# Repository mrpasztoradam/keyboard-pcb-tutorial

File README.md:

# keyboard-pcb-tutorial
 Keyboard design from 0

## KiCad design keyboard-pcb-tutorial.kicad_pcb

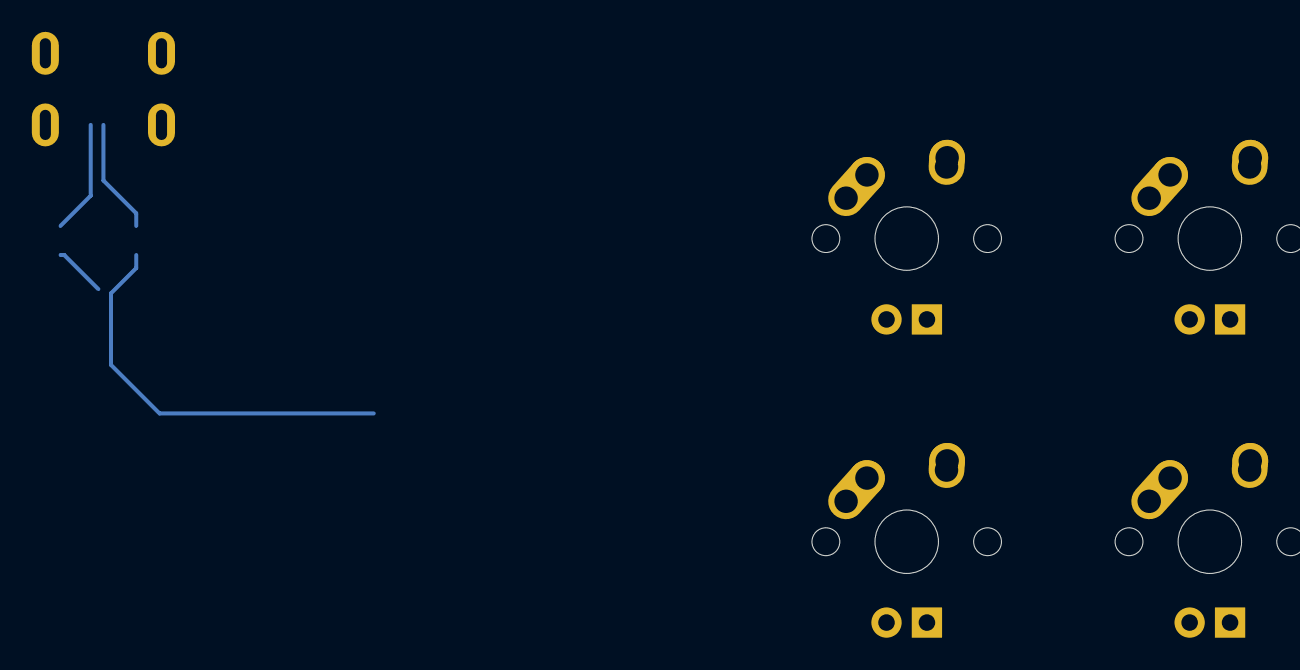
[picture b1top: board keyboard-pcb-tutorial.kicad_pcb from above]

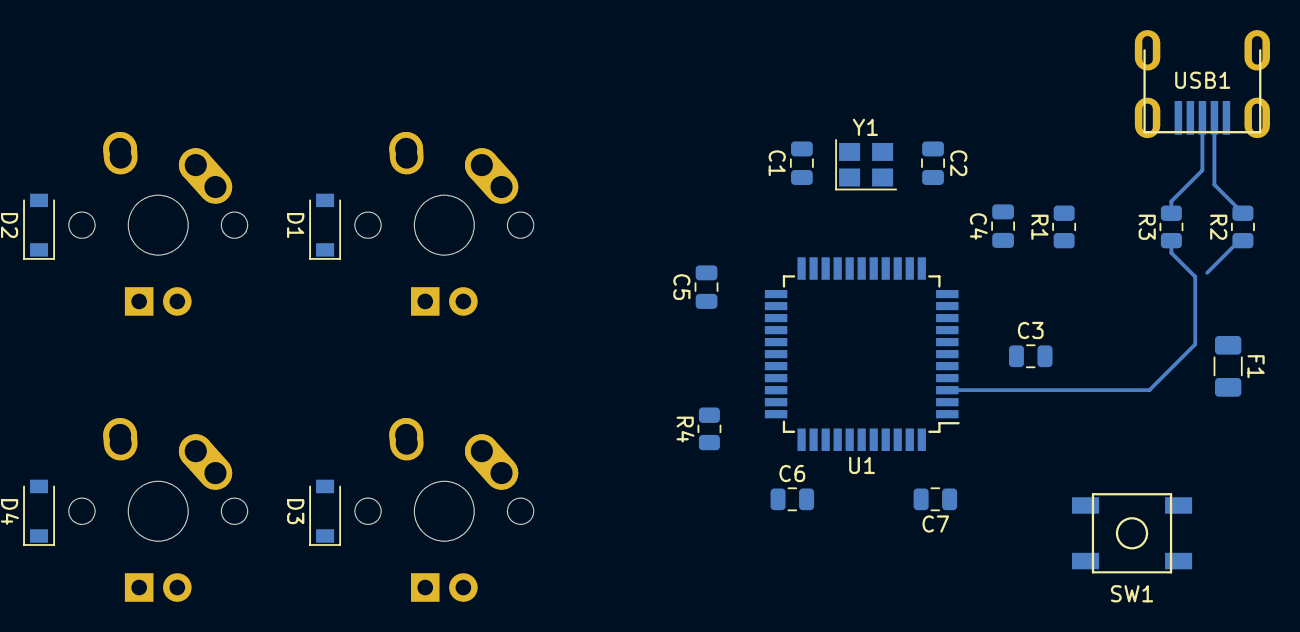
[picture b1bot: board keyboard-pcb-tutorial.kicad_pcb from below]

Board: 2 copper layers, 24 parts (20 on the bottom side), 20 nets.

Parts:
C1, C2: 22pF; C_0805_2012Metric
C3: C_Small; C_0805_2012Metric
C4, C5, C6: 0.1uF; C_0805_2012Metric
C7: 0.10uF; C_0805_2012Metric
D1, D2, D3, D4: D_Small; D_SOD-123
F1: Polyfuse_Small; Fuse_1206_3216Metric
MX1, MX2, MX3, MX4: MX-NoLED; MX-1U
R1, R4: 10k; R_0805_2012Metric
R2, R3: 22; R_0805_2012Metric
SW1: SW_Push; SKQG-1155865
U1: ATmega32U4-AU; TQFP-44_10x10mm_P0.8mm
USB1: Molex-0548190589
Y1: 16Mhz; Crystal_SMD_3225-4Pin_3.2x2.5mm

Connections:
+5V: C4.1, C5.1, C6.1, C7.1, F1.1, R1.2, U1.2, U1.7, U1.14, U1.24, U1.34, U1.44
COL0: MX1.1, MX3.1
COL1: MX2.1, MX4.1
D+: R2.2, USB1.3
D-: R3.2, USB1.4
GND: C1.2, C2.2, C3.2, C4.2, C5.2, C6.2, C7.2, R4.1, SW1.1, U1.5, U1.15, U1.23, U1.35, U1.43, USB1.1, Y1.2, Y1.4
unnamed: C1.1, U1.17, Y1.1
unnamed: C2.1, U1.16, Y1.3
unnamed: C3.1, U1.6
unnamed: D1.2, MX1.2
unnamed: D2.2, MX2.2
unnamed: D3.2, MX3.2
unnamed: D4.2, MX4.2
unnamed: R1.1, SW1.2, U1.13
unnamed: R2.1, U1.4
unnamed: R3.1, U1.3
unnamed: R4.2, U1.33
ROW0: D1.1, D2.1
ROW1: D3.1, D4.1
VCC: F1.2, USB1.5

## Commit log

2021-07-01 Initialize project
    initial commit
2021-07-01 Add submodules
2021-07-01 Add libraries
    added project specific libraries
2021-07-01 PCB footprints
    Assigned PCB footprints
2021-07-01 Started PCB routing
2021-07-05 Add promicro submodule
